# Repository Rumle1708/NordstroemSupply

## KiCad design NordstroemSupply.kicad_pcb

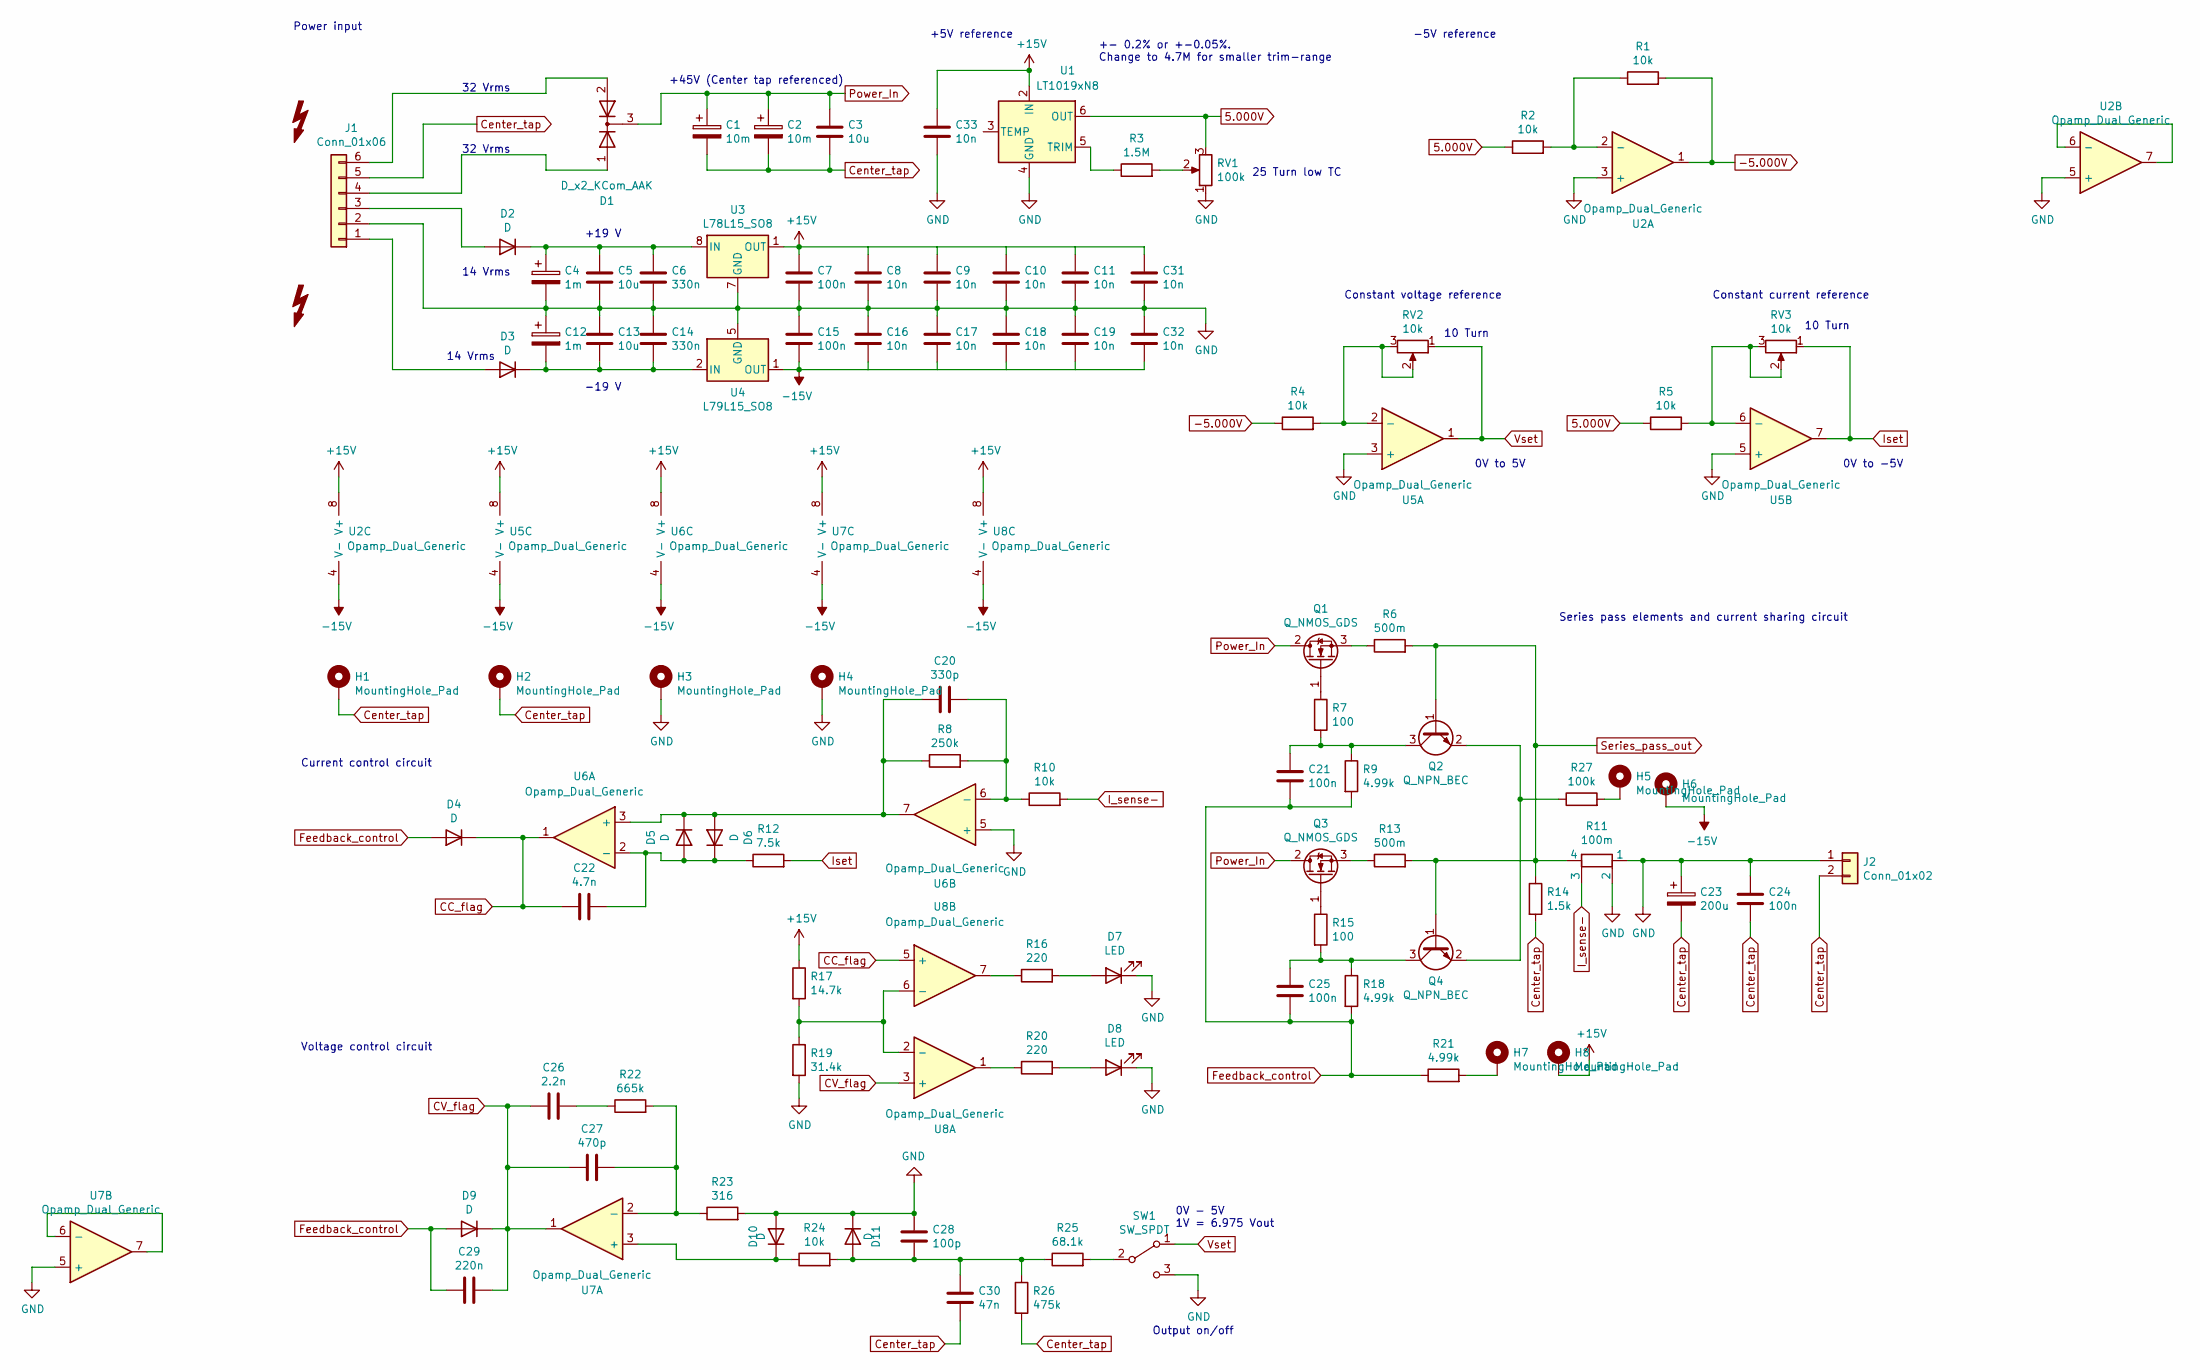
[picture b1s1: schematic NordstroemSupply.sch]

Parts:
C1, C2: 10m; CP_Radial_D35.0mm_P10.00mm_SnapIn
C3, C5, C13: 10u; C_1210_3225Metric
C4, C12: 1m; CP_Elec_16x17.5
C6, C14: 330n; C_0805_2012Metric
C7, C15, C21, C24, C25: 100n; C_0805_2012Metric
C8, C9, C10, C11, C16, C17, C18, C19, C31, C32, C33: 10n; C_0805_2012Metric
C20: 330p; C_0805_2012Metric
C22: 4.7n; C_0805_2012Metric
C23: 200u; CP_Elec_10x10.5
C26: 2.2n; C_0805_2012Metric
C27: 470p; C_0805_2012Metric
C28: 100p; C_0805_2012Metric
C29: 220n; C_0805_2012Metric
C30: 47n; C_0805_2012Metric
D1: D_x2_KCom_AAK; TO-277A
D2, D3, D4, D5, D6, D9, D10, D11: D; D_SOD-123
D7, D8: LED; LED_D5.0mm
H1, H2, H3, H4: MountingHole_Pad; MountingHole_3.2mm_M3_Pad_Via
H5, H6, H7, H8: MountingHole_Pad; TestPoint_THTPad_1.5x1.5mm_Drill0.7mm
J1: Conn_01x06; TerminalBlock_RND_205-00236_1x06_P5.08mm_Horizontal
J2: Conn_01x02; TerminalBlock_RND_205-00232_1x02_P5.08mm_Horizontal
Q1, Q3: Q_NMOS_GDS; TO-247-3_Vertical
Q2, Q4: Q_NPN_BEC; SOT-23
R1, R2, R4, R5, R10, R24: 10k; R_0805_2012Metric
R3: 1.5M; R_0805_2012Metric
R6, R13: 500m; R_2512_6332Metric
R7, R15: 100; R_0805_2012Metric
R8: 250k; R_0805_2012Metric
R9, R18, R21: 4.99k; R_0805_2012Metric
R11: 100m; LVK20
R12: 7.5k; C_0805_2012Metric
R14: 1.5k; R_2816_7142Metric
R16, R20: 220; R_0805_2012Metric
R17: 14.7k; R_0805_2012Metric
R19: 31.4k; R_0805_2012Metric
R22: 665k; R_0805_2012Metric
R23: 316; R_0805_2012Metric
R25: 68.1k; R_0805_2012Metric
R26: 475k; R_0805_2012Metric
R27: 100k; R_0805_2012Metric
RV1: 100k; Potentiometer_Bourns_3296W_Vertical
RV2, RV3: 10k; PinSocket_1x03_P2.54mm_Vertical
SW1: SW_SPDT; PinSocket_1x03_P2.54mm_Vertical
U1: LT1019xN8; SO-8_3.9x4.9mm_P1.27mm
U2, U5, U6, U7, U8: Opamp_Dual_Generic; SOIC-8_3.9x4.9mm_P1.27mm
U3: L78L15_SO8; SOIC-8_3.9x4.9mm_P1.27mm
U4: L79L15_SO8; SOIC-8_3.9x4.9mm_P1.27mm

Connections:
5.000V: R2.1, R5.1, RV1.3, U1.6 (OUT)
+15V: C7.1, C8.1, C9.1, C10.1, C11.1, C31.1, C33.1, H8.1, R17.1, U1.2 (IN), U2.8 (V+), U3.1 (OUT), U5.8 (V+), U6.8 (V+), U7.8 (V+), U8.8 (V+)
-5.000V: R1.2, R4.1, U2.1
-15V: C15.2, C16.2, C17.2, C18.2, C19.2, C32.2, H6.1, U2.4 (V-), U4.1 (OUT), U5.4 (V-), U6.4 (V-), U7.4 (V-), U8.4 (V-)
CC_flag: C22.2, D4.1 (K), U6.1, U8.5 (+)
CV_flag: C26.2, C27.2, C29.1, D9.1 (K), U7.1, U8.3 (+)
Center_tap: C1.2, C2.2, C3.2, C23.2, C24.2, C30.2, H1.1, H2.1, J1.5, J2.2, R14.2, R26.2
Feedback_control: C21.2, C25.2, C29.2, D4.2 (A), D9.2 (A), R9.2, R18.2, R21.1
GND: C4.2, C5.2, C6.2, C7.2, C8.2, C9.2, C10.2, C11.2, C12.1, C13.1, C14.1, C15.1, C16.1, C17.1, C18.1, C19.1, C23.1, C24.1, C28.1, C31.2, C32.1, C33.2, D7.1 (K), D8.1 (K), D10.2 (A), D11.1 (K), H3.1, H4.1, J1.2, J2.1, R11.1, R11.2, R19.2, R23.2, RV1.1, SW1.3 (C), U1.4 (GND), U2.3 (+), U2.5 (+), U3.2 (GND), U3.3 (GND), U3.6 (GND), U3.7 (GND), U4.5 (GND), U5.3 (+), U5.5 (+), U6.5 (+), U7.5 (+)
I_sense-: R10.2, R11.3
Iset: R12.2, RV3.1, U5.7
unnamed: C4.1, C5.1, C6.1, D2.1 (K), U3.8 (IN)
unnamed: C12.2, C13.2, C14.2, D3.1 (K), U4.2 (IN), U4.3 (IN), U4.6 (IN), U4.7 (IN)
unnamed: C20.1, R8.2, R10.1, U6.6 (-)
unnamed: C20.2, D5.1 (K), D6.2 (A), R8.1, U6.3 (+), U6.7
unnamed: C21.1, Q2.3 (C), R7.2, R9.1
unnamed: C22.1, D5.2 (A), D6.1 (K), R12.1, U6.2 (-)
unnamed: C25.1, Q4.3 (C), R15.2, R18.1
unnamed: C26.1, R22.1
unnamed: C27.1, R22.2, R23.1, U7.2 (-)
unnamed: C28.2, C30.1, D11.2 (A), R24.2, R25.1, R26.1
unnamed: D1.1 (A), J1.4
unnamed: D1.2 (A), J1.6
unnamed: D2.2 (A), J1.3
unnamed: D3.2 (A), J1.1
unnamed: D7.2 (A), R16.2
unnamed: D8.2 (A), R20.2
unnamed: D10.1 (K), R24.1, U7.3 (+)
unnamed: H5.1, R27.2
unnamed: H7.1, R21.2
unnamed: Q1.1 (G), R7.1
unnamed: Q1.3 (S), R6.1
unnamed: Q2.2 (E), Q4.2 (E), R27.1
unnamed: Q3.1 (G), R15.1
unnamed: Q3.3 (S), R13.1
unnamed: R1.1, R2.2, U2.2 (-)
unnamed: R3.1, U1.5 (TRIM)
unnamed: R3.2, RV1.2
unnamed: R4.2, RV2.2, RV2.3, U5.2 (-)
unnamed: R5.2, RV3.2, RV3.3, U5.6 (-)
unnamed: R16.1, U8.7
unnamed: R17.2, R19.1, U8.2 (-), U8.6 (-)
unnamed: R20.1, U8.1
unnamed: R25.2, SW1.2 (B)
unnamed: U2.6 (-), U2.7
unnamed: U7.6 (-), U7.7
Power_In: C1.1, C2.1, C3.1, D1.3 (K), Q1.2 (D), Q3.2 (D)
Series_pass_out: Q2.1 (B), Q4.1 (B), R6.2, R11.4, R13.2, R14.1
Vset: RV2.1, SW1.1 (A), U5.1

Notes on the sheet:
32 Vrms
+45V (Center tap referenced)
-19 V
+19 V
14 Vrms
0V to -5V
10 Turn
25 Turn low TC
0V to 5V
+- 0.2% or +-0.05%. Change to 4.7M for smaller trim-range
Series pass elements and current sharing circuit
Constant current reference
Constant voltage reference
-5V reference
+5V reference
Power input
Current control circuit
Voltage control circuit
Output on/off
0V - 5V 1V = 6.975 Vout

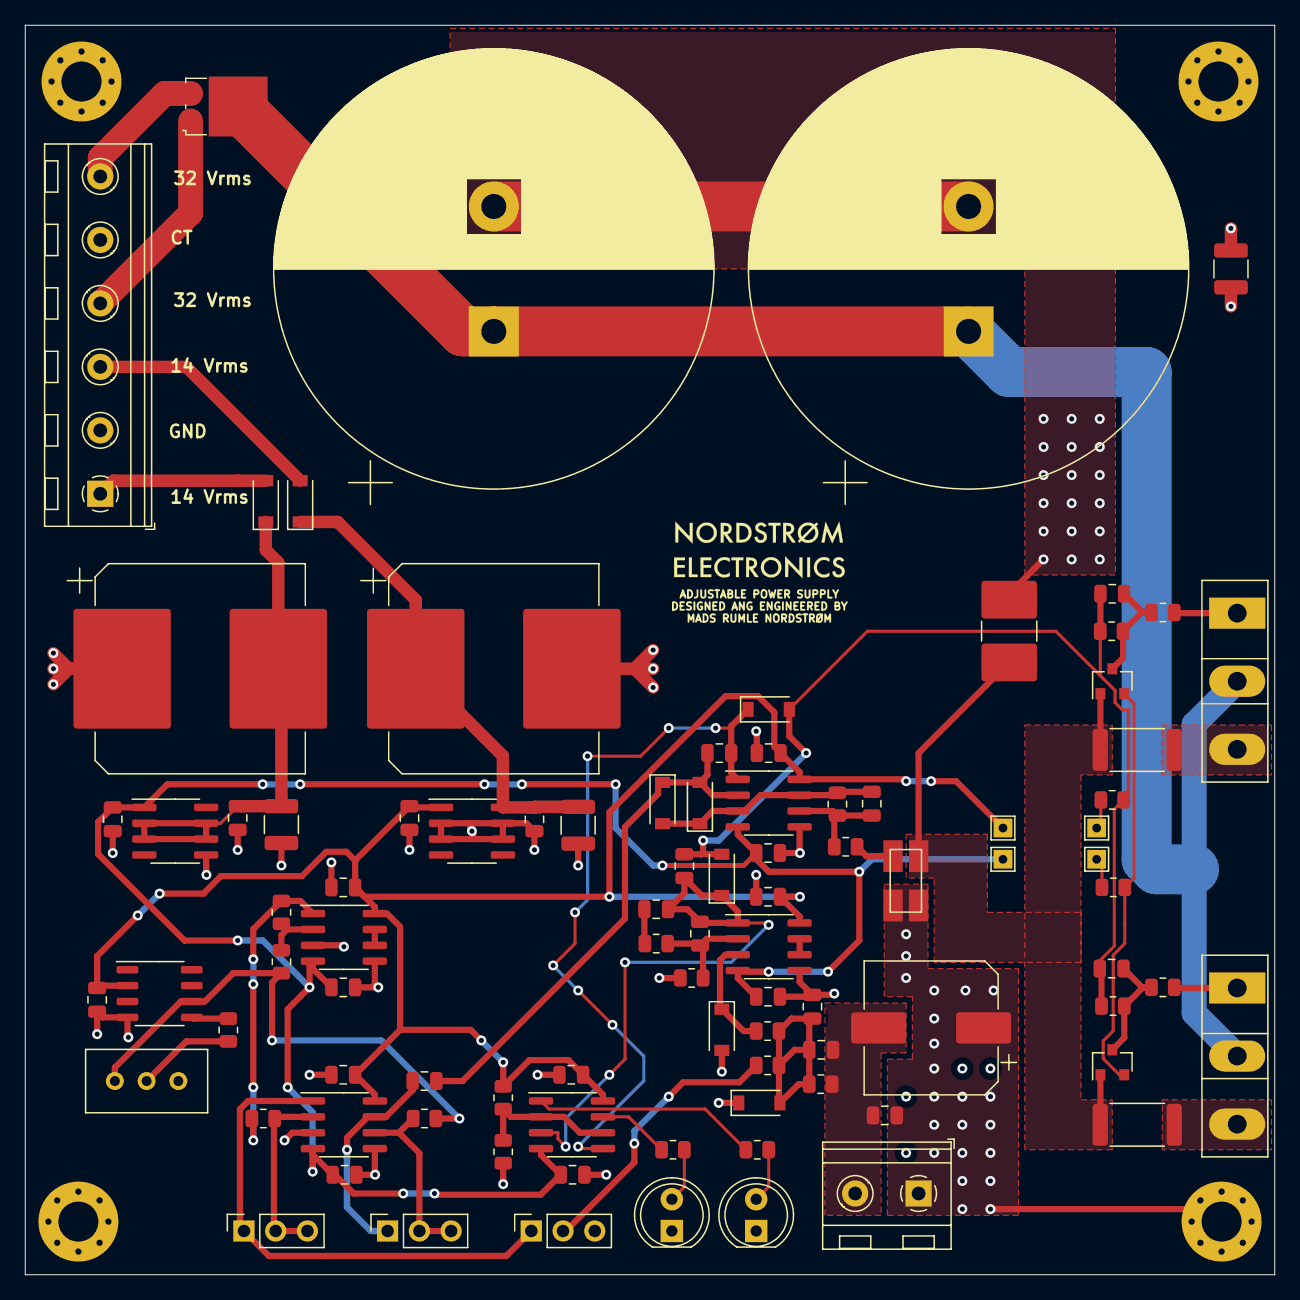
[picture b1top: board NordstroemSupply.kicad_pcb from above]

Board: 2 copper layers, 100.0 x 100.0 mm, 97 parts (0 on the bottom side), 49 nets.

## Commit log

2021-12-23 First version
